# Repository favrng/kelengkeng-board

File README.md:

# kelengkeng-board

This project is one of my 5 work programs during field community service (KKN-PPM UGM Periode 4 Tahun 2022). I remade the board for automatic plant waterer that was previously broken.

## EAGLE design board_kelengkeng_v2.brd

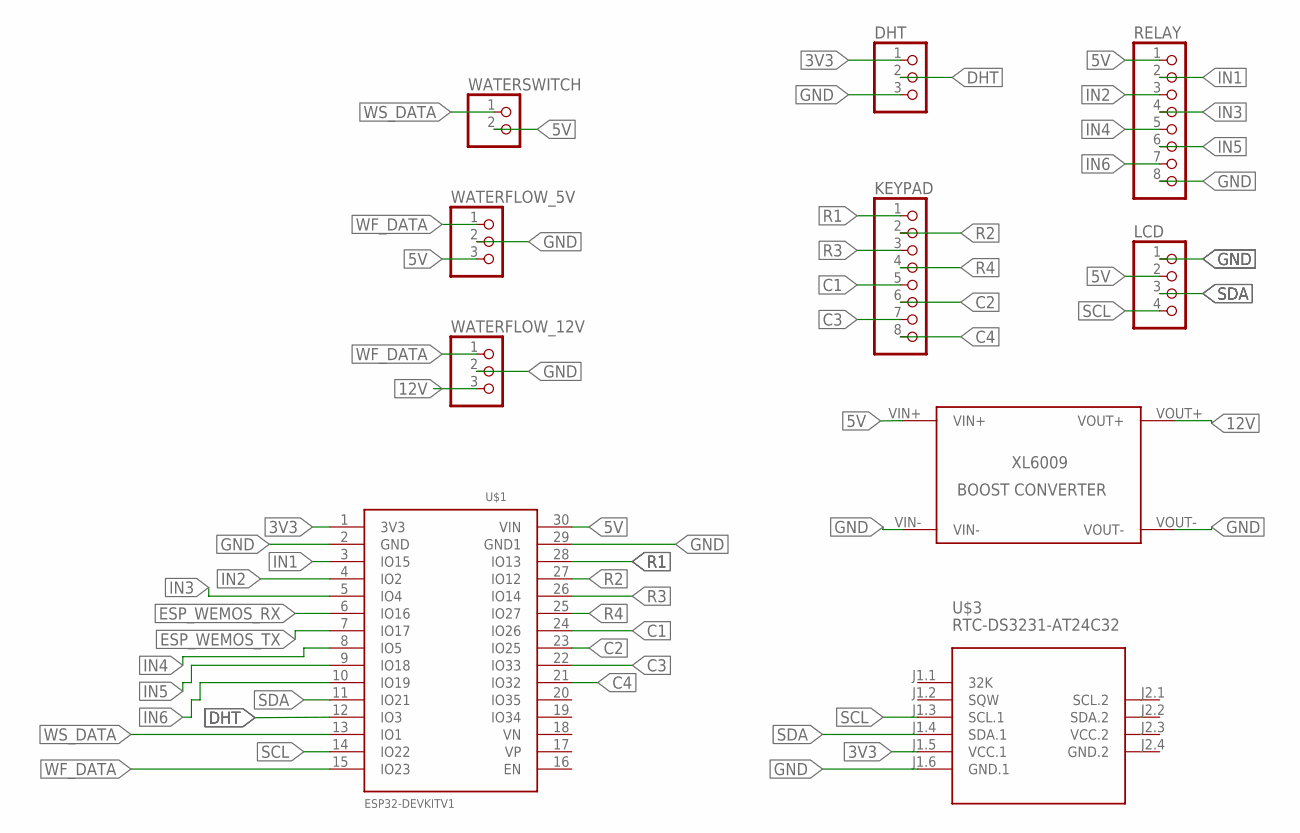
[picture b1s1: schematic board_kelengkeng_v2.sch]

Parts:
DHT: PINHD-1X3; 1X03
KEYPAD: PINHD-1X8; 1X08
LCD: PINHD-1X4; 1X04
RELAY: PINHD-1X8; 1X08
U$1: ESP32DEVKITV1; ESP32-DEVKITV1
U$2: XL6009
U$3: RTC-DS3231-AT24C32
WATERFLOW_5V, WATERFLOW_12V: PINHD-1X3; 1X03
WATERSWITCH: PINHD-1X2; 1X02

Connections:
3V3: DHT.1, U$1.1 (3V3), U$3.J1.5 (VCC.1)
5V: LCD.2, RELAY.1, U$1.30 (VIN), U$2.VIN+, WATERFLOW_5V.3, WATERSWITCH.2
12V: U$2.VOUT+, WATERFLOW_12V.3
C1: KEYPAD.5, U$1.24 (IO26)
C2: KEYPAD.6, U$1.23 (IO25)
C3: KEYPAD.7, U$1.22 (IO33)
C4: KEYPAD.8, U$1.21 (IO32)
DHT: DHT.2, U$1.12 (IO3)
ESP_WEMOS_RX: U$1.6 (IO16)
ESP_WEMOS_TX: U$1.7 (IO17)
GND.2: U$3.J2.4 (GND.2)
IN1: RELAY.2, U$1.3 (IO15)
IN2: RELAY.3, U$1.4 (IO2)
IN3: RELAY.4, U$1.5 (IO4)
IN4: RELAY.5, U$1.8 (IO5)
IN5: RELAY.6, U$1.9 (IO18)
IN6: RELAY.7, U$1.10 (IO19)
R1: KEYPAD.1, U$1.28 (IO13)
R2: KEYPAD.2, U$1.27 (IO12)
R3: KEYPAD.3, U$1.26 (IO14)
R4: KEYPAD.4, U$1.25 (IO27)
SCL: LCD.4, U$1.14 (IO22), U$3.J1.3 (SCL.1)
SDA: LCD.3, U$1.11 (IO21), U$3.J1.4 (SDA.1)
VCC.2: U$3.J2.3 (VCC.2)
WF_DATA: U$1.15 (IO23), WATERFLOW_5V.1, WATERFLOW_12V.1
WS_DATA: U$1.13 (IO1), WATERSWITCH.1

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
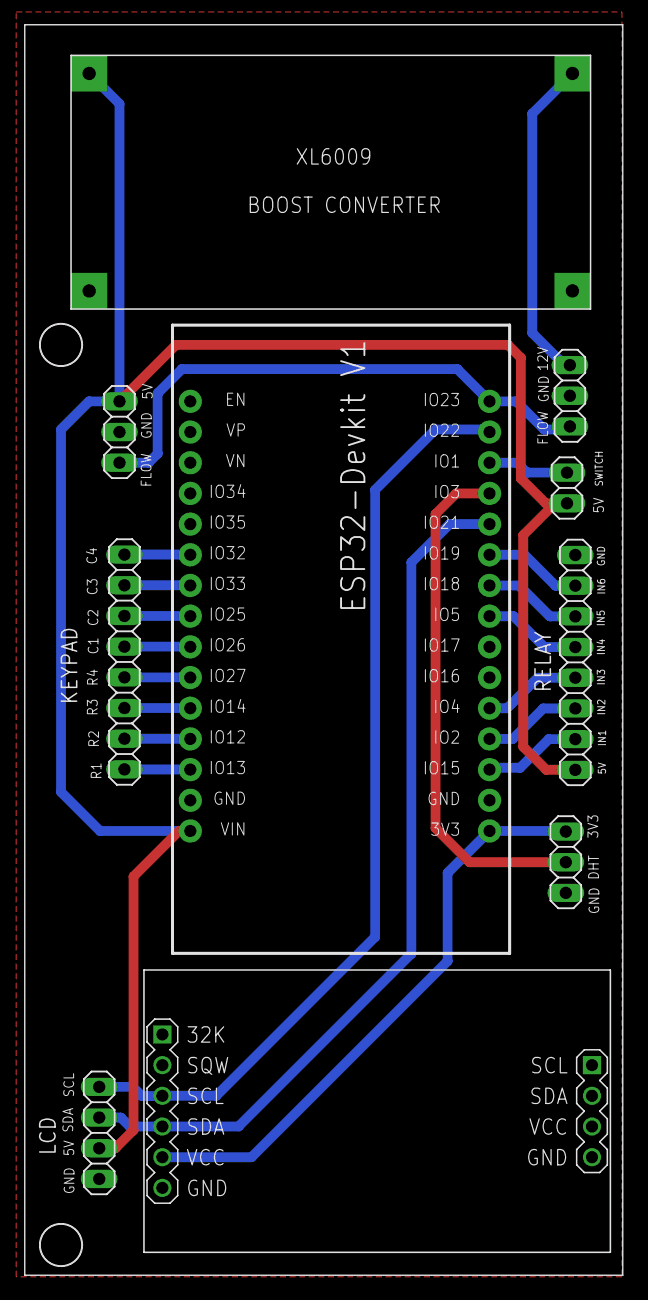
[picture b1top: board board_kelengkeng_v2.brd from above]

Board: 2 copper layers, 49.5 x 103.5 mm, 10 parts (0 on the bottom side), 23 nets.

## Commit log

2023-11-02 Added files

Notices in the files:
parts and their libraries:
diy-modules: Released under the Creative Commons Attribution 4.0 International License: http://creativecommons.org/licenses/by/4.0
